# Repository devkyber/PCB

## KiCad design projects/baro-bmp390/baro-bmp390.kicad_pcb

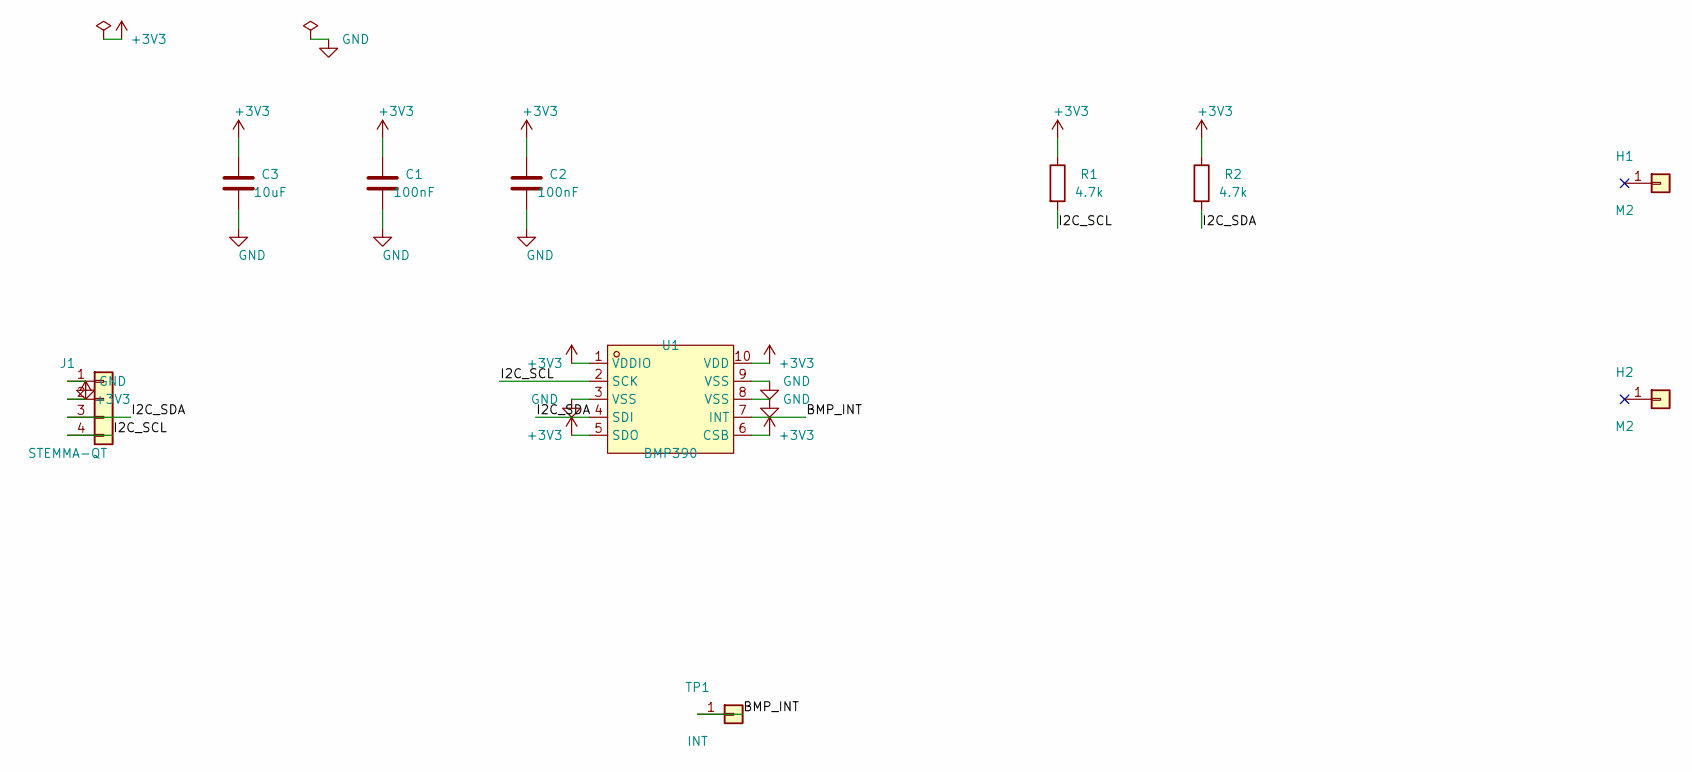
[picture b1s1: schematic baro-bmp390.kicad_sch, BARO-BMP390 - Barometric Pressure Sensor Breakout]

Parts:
C1, C2: 100nF; C_0402_1005Metric
C3: 10uF; C_0603_1608Metric
H1, H2: M2; MountingHole_2.2mm_M2_Pad
J1: STEMMA-QT; JST_SH_SM04B-SRSS-TB_1x04-1MP_P1.00mm_Horizontal
R1, R2: 4.7k; R_0402_1005Metric
TP1: INT; TestPoint_Pad_1.0x1.0mm
U1: BMP390; LGA-10_L2.0-W2.0-P0.50-BL

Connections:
+3V3: C1.1, C2.1, C3.1, J1.2, R1.1, R2.1, U1.1 (VDDIO), U1.5 (SDO), U1.6 (CSB), U1.10 (VDD)
BMP_INT: TP1.1, U1.7 (INT)
GND: C1.2, C2.2, C3.2, J1.1, U1.3 (VSS), U1.8 (VSS), U1.9 (VSS)
I2C_SCL: J1.4, R1.2, U1.2 (SCK)
I2C_SDA: J1.3, R2.2, U1.4 (SDI)

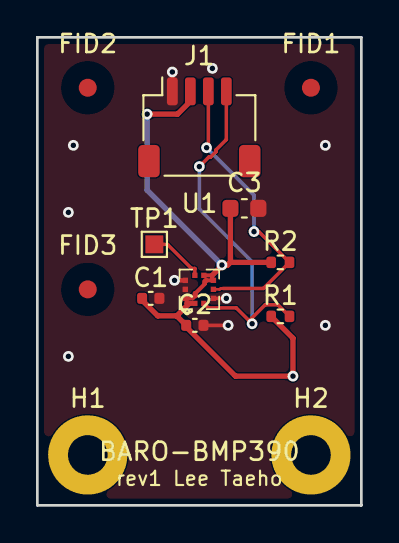
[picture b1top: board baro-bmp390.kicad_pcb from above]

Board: 2 copper layers, 18.0 x 26.0 mm, 13 parts (0 on the bottom side), 5 nets.

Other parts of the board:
FID1, FID2, FID3: FIDUCIAL; Fiducial_1mm_Mask3mm

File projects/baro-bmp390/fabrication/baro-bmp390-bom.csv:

Comment,Designator,Footprint,LCSC Part #
100nF,"C1,C2",C_0402_1005Metric,C307331
10uF,C3,C_0603_1608Metric,C96446
4.7k,"R1,R2",R_0402_1005Metric,C25900
BMP390,U1,LGA-10_L2.0-W2.0-P0.50-BL,C5124834
STEMMA-QT,J1,JST_SH_SM04B-SRSS-TB_1x04-1MP_P1.00mm_Horizontal,C160404

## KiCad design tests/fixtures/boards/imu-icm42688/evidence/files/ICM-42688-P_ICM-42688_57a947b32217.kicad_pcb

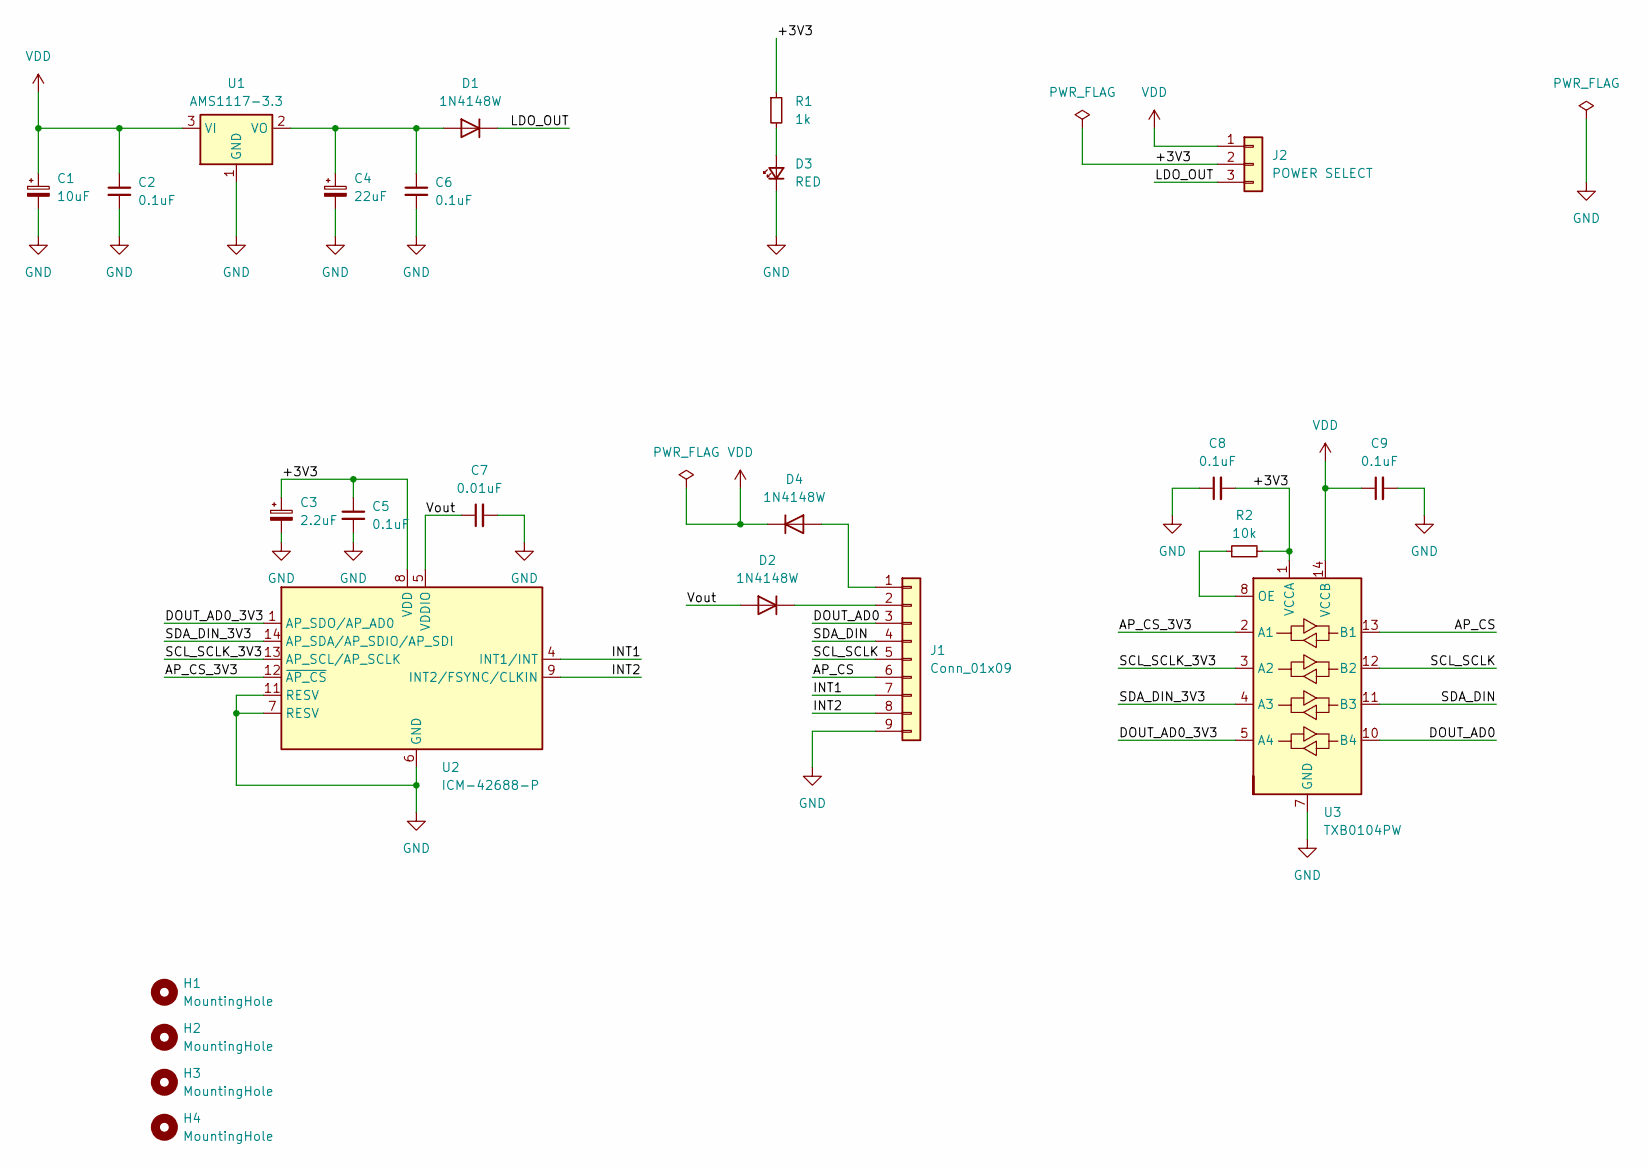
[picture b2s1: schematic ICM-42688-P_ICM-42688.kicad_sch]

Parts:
C1: 10uF; CP_EIA-3528-12_Kemet-T
C2, C5, C6, C8, C9: 0.1uF; C_0603_1608Metric
C3: 2.2uF; CP_EIA-3528-12_Kemet-T
C4: 22uF; CP_EIA-3528-12_Kemet-T
C7: 0.01uF; C_0603_1608Metric
D1, D2, D4: 1N4148W; D_SOD-123
D3: RED; LED_0603_1608Metric
H1, H2, H3, H4: MountingHole; MountingHole_2mm
J1: Conn_01x09; PinHeader_1x09_P2.54mm_Vertical
J2: POWER SELECT; PinHeader_1x03_P2.54mm_Vertical
R1: 1k; R_0603_1608Metric
R2: 10k; R_0603_1608Metric
U1: AMS1117-3.3; SOT-223-3_TabPin2
U2: ICM-42688-P; LGA-14_3x2.5mm_P0.5mm_LayoutBorder3x4y
U3: TXB0104PW; TSSOP-14_4.4x5mm_P0.65mm

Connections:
/+3V3: C3.1, C5.1, C8.2, J2.2, R1.1, R2.2, U2.8 (VDD), U3.1 (VCCA)
/AP_CS: J1.6, U3.13 (B1)
/AP_CS_3V3: U2.12 (~AP_CS), U3.2 (A1)
/DOUT_AD0: J1.3, U3.10 (B4)
/DOUT_AD0_3V3: U2.1 (AP_SDO/AP_AD0), U3.5 (A4)
/INT1: J1.7, U2.4 (INT1/INT)
/INT2: J1.8, U2.9 (INT2/FSYNC/CLKIN)
/LDO_OUT: D1.1 (K), J2.3
/SCL_SCLK: J1.5, U3.12 (B2)
/SCL_SCLK_3V3: U2.13 (AP_SCL/AP_SCLK), U3.3 (A2)
/SDA_DIN: J1.4, U3.11 (B3)
/SDA_DIN_3V3: U2.14 (AP_SDA/AP_SDIO/AP_SDI), U3.4 (A3)
/Vout: C7.1, D2.2 (A), U2.5 (VDDIO)
GND: C1.2, C2.2, C3.2, C4.2, C5.2, C6.2, C7.2, C8.1, C9.2, D3.1 (K), J1.9, U1.1 (GND), U2.6 (GND), U2.7 (RESV), U2.11 (RESV), U3.7 (GND)
unnamed: C4.1, C6.1, D1.2 (A), U1.2 (VO)
unnamed: D2.1 (K), J1.2
unnamed: D3.2 (A), R1.2
unnamed: D4.2 (A), J1.1
unnamed: R2.1, U3.8 (OE)
VDD: C1.1, C2.1, C9.1, D4.1 (K), J2.1, U1.3 (VI), U3.14 (VCCB)

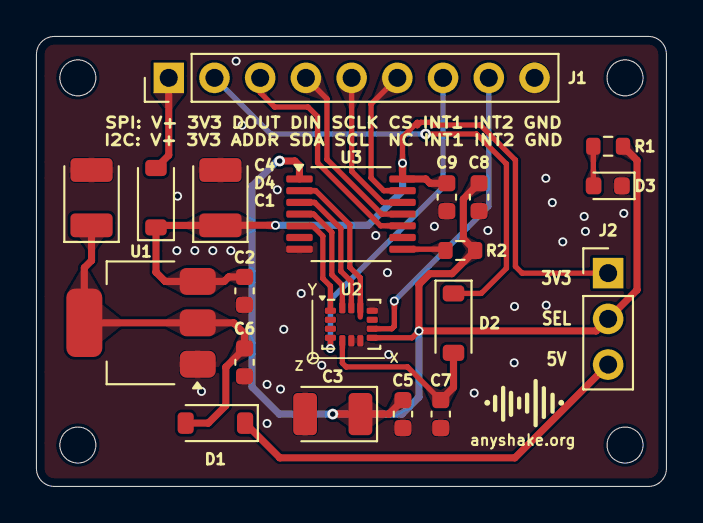
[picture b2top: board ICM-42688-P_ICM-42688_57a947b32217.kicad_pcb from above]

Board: 2 copper layers, 35.0 x 25.0 mm, 24 parts (0 on the bottom side), 20 nets.

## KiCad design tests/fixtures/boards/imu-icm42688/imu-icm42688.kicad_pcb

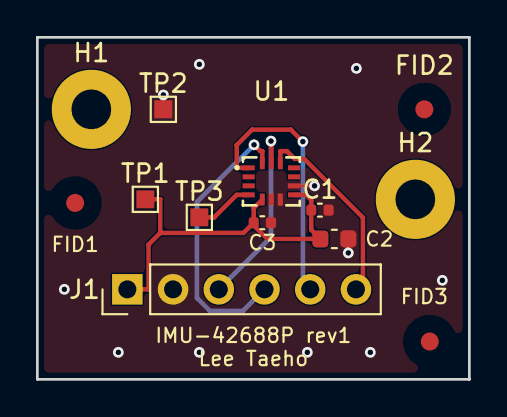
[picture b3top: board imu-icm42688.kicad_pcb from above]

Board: 2 copper layers, 24.0 x 19.0 mm, 13 parts (0 on the bottom side), 7 nets.

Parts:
C1: 100nF; C_0402_1005Metric
C2: 2.2uF; C_0603_1608Metric
C3: 10nF; C_0402_1005Metric
FID1, FID2, FID3: FIDUCIAL; Fiducial_1mm_Mask3mm
H1, H2: M2; MountingHole_2.2mm_M2_Pad
J1: SPI-HDR; PinHeader_1x06_P2.54mm_Vertical
TP1: +3V3; TestPoint_Pad_1.0x1.0mm
TP2: GND; TestPoint_Pad_1.0x1.0mm
TP3: INT1; TestPoint_Pad_1.0x1.0mm
U1: ICM-42688-P; LGA-14_L3.0-W2.5-P0.50-TL

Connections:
+3V3: C1.1, C2.1, C3.1, J1.1, TP1.1, U1.5, U1.8
GND: C1.2, C2.2, C3.2, J1.2, TP2.1, U1.6, U1.7, U1.9
INT1: TP3.1, U1.4
SPI_CS: J1.6, U1.12
SPI_SCLK: J1.3, U1.13
SPI_SDI: J1.4, U1.14
SPI_SDO: J1.5, U1.1

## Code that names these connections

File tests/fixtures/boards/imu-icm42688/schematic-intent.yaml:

schema_version: 1
title: ICM-42688-P SPI breakout
revision: working-1
sheets:
  - id: main
    title: Host interface, inertial sensor and mounting
    page: A4
blocks:
  - id: host
    title: Host SPI and supplied rails
    sheet: main
    flow_order: 1
    placement_hint: left
  - id: sensor
    title: ICM-42688-P and decoupling
    sheet: main
    flow_order: 2
    placement_hint: center
  - id: mechanical
    title: Mounting - owner orientation pending
    sheet: main
    flow_order: 3
    placement_hint: right
components:
  - ref: J1
    value: SPI-HDR
    symbol: Connector_Generic:Conn_01x06
    footprint: Connector_PinHeader_2.54mm:PinHeader_1x06_P2.54mm_Vertical
    block: host
    evidence_part_number: GENERIC-SPI-HEADER-1X06
    pin_map_evidence_id: null
    pin_map_review_note: Preserved accepted Conn_01x06 symbol and netmap; vendor connector numbering and mating orientation remain unverified.
    pins:
      '1': {net: '+3V3', style: power}
      '2': {net: GND, style: power}
      '3': {net: SPI_SCLK, style: label}
      '4': {net: SPI_SDI, style: label}
      '5': {net: SPI_SDO, style: label}
      '6': {net: SPI_CS, style: label}
    pin_inventory: ['1', '2', '3', '4', '5', '6']
  - ref: TP1
    value: '+3V3'
    symbol: Connector_Generic:Conn_01x01
    footprint: TestPoint:TestPoint_Pad_1.0x1.0mm
    block: host
    evidence_part_number: GENERIC-TEST-PAD-1MM
    pin_map_evidence_id: null
    pin_map_review_note: Preserved accepted Conn_01x01 symbol and single-pad footprint; no matching vendor drawing is archived, physical verification remains pending.
    pins:
      '1': {net: '+3V3', style: power}
    pin_inventory: ['1']
  - ref: TP2
    value: GND
    symbol: Connector_Generic:Conn_01x01
    footprint: TestPoint:TestPoint_Pad_1.0x1.0mm
    block: host
    evidence_part_number: GENERIC-TEST-PAD-1MM
    pin_map_evidence_id: null
    pin_map_review_note: Preserved accepted Conn_01x01 symbol and single-pad footprint; no matching vendor drawing is archived, physical verification remains pending.
    pins:
      '1': {net: GND, style: power}
    pin_inventory: ['1']
  - ref: '#FLG01'
    value: PWR_FLAG
    symbol: power:PWR_FLAG
    footprint: '~'
    block: host
    evidence_part_number: KICAD-PWR-FLAG
    pin_map_evidence_id: null
    pin_map_review_note: Preserved accepted KiCad power flag asserting the host-supplied rail; this is an ERC assertion without a vendor component or physical footprint.
    pins:
      '1': {net: '+3V3', style: power}
    pin_inventory: ['1']
  - ref: '#FLG02'
    value: PWR_FLAG
    symbol: power:PWR_FLAG
    footprint: '~'
    block: host
    evidence_part_number: KICAD-PWR-FLAG
    pin_map_evidence_id: null
    pin_map_review_note: Preserved accepted KiCad power flag asserting the host ground; this is an ERC assertion without a vendor component or physical footprint.
    pins:
      '1': {net: GND, style: power}
    pin_inventory: ['1']
  - ref: U1
    value: ICM-42688-P
    symbol: jlcpcb:ICM-42688-P
    footprint: jlcpcb:LGA-14_L3.0-W2.5-P0.50-TL
    block: sensor
    evidence_part_number: ICM-42688-P
    pin_map_evidence_id: sha256:5710af9388adbb311557e99203e5834e17fb0b6e16baf9c09a8bce18b2ce1b9c
    pins:
      '1': {net: SPI_SDO, style: label}
      '4': {net: INT1, style: wire}
      '5': {net: '+3V3', style: power}
      '6': {net: GND, style: power}
      '7': {net: GND, style: power}
      '8': {net: '+3V3', style: power}
      '9': {net: GND, style: power}
      '12': {net: SPI_CS, style: label}
      '13': {net: SPI_SCLK, style: label}
      '14': {net: SPI_SDI, style: label}
    no_connects:
      - {pin: '2', reason: Accepted schematic NC retained; DS-000347 rev 1.6 Table 10 page 20 permits NC or GND for this reserved pin.}
      - {pin: '3', reason: Accepted schematic NC retained; DS-000347 rev 1.6 Table 10 page 20 permits NC or GND for this reserved pin.}
      - {pin: '10', reason: Accepted schematic NC retained; DS-000347 rev 1.6 Table 10 page 20 permits NC or GND for this reserved pin.}
      - {pin: '11', reason: Accepted schematic NC retained; DS-000347 rev 1.6 Table 10 page 20 permits NC or GND for this reserved pin.}
    pin_inventory: ['1', '2', '3', '4', '5', '6', '7', '8', '9', '10', '11', '12', '13', '14']
  - ref: TP3
    value: INT1
    symbol: Connector_Generic:Conn_01x01
    footprint: TestPoint:TestPoint_Pad_1.0x1.0mm
    block: sensor
    evidence_part_number: GENERIC-TEST-PAD-1MM
    pin_map_evidence_id: null
    pin_map_review_note: Preserved accepted Conn_01x01 symbol and single-pad footprint; no matching vendor drawing is archived, physical verification remains pending.
    pins:
      '1': {net: INT1, style: wire}
    pin_inventory: ['1']
  - ref: C1
    value: 100nF
    symbol: Device:C
    footprint: Capacitor_SMD:C_0402_1005Metric
    block: sensor
    evidence_part_number: GENERIC-100NF-0402
    pin_map_evidence_id: null
    pin_map_review_note: Preserved accepted Device:C pin numbering and 0402 footprint; sensor datasheet supports circuit value, not a specific purchased capacitor pin map. Vendor package verification remains pending.
    pins:
      '1': {net: '+3V3', style: power}
      '2': {net: GND, style: power}
    pin_inventory: ['1', '2']
  - ref: C2
    value: 2.2uF
    symbol: Device:C
    footprint: Capacitor_SMD:C_0603_1608Metric
    block: sensor
    evidence_part_number: GENERIC-2.2UF-0603
    pin_map_evidence_id: null
    pin_map_review_note: Preserved accepted Device:C pin numbering and 0603 footprint; sensor datasheet supports circuit value, not a specific purchased capacitor pin map. Vendor package verification remains pending.
    pins:
      '1': {net: '+3V3', style: power}
      '2': {net: GND, style: power}
    pin_inventory: ['1', '2']
  - ref: C3
    value: 10nF
    symbol: Device:C
    footprint: Capacitor_SMD:C_0402_1005Metric
    block: sensor
    evidence_part_number: GENERIC-10NF-0402
    pin_map_evidence_id: null
    pin_map_review_note: Preserved accepted Device:C pin numbering and 0402 footprint; sensor datasheet supports circuit value, not a specific purchased capacitor pin map. Vendor package verification remains pending.
    pins:
      '1': {net: '+3V3', style: power}
      '2': {net: GND, style: power}
    pin_inventory: ['1', '2']
  - ref: H1
    value: M2
    symbol: Connector_Generic:Conn_01x01
    footprint: MountingHole:MountingHole_2.2mm_M2_Pad
    block: mechanical
    evidence_part_number: GENERIC-M2-PLATED-MOUNTING-HOLE
    pin_map_evidence_id: null
    pin_map_review_note: Preserved accepted Conn_01x01 symbol and plated M2 hole footprint; mechanical drawing and assembly verification remain pending.
    pins: {}
    no_connects:
      - {pin: '1', reason: Accepted schematic explicitly marks the mounting-hole pad NC; no ground connection is added.}
    pin_inventory: ['1']
  - ref: H2
    value: M2
    symbol: Connector_Generic:Conn_01x01
    footprint: MountingHole:MountingHole_2.2mm_M2_Pad
    block: mechanical
    evidence_part_number: GENERIC-M2-PLATED-MOUNTING-HOLE
    pin_map_evidence_id: null
    pin_map_review_note: Preserved accepted Conn_01x01 symbol and plated M2 hole footprint; mechanical drawing and assembly verification remain pending.
    pins: {}
    no_connects:
      - {pin: '1', reason: Accepted schematic explicitly marks the mounting-hole pad NC; no ground connection is added.}
    pin_inventory: ['1']
boundary_nets: [SPI_SCLK, SPI_SDI, SPI_SDO, SPI_CS]

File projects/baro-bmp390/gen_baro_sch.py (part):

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      desc='STEMMA QT / Qwiic I2C connector, JST SH 4-pin 1mm pitch')
pin_label('J1', '1', 'GND')
pin_label('J1', '2', '+3V3')
pin_label('J1', '3', 'I2C_SDA')
pin_label('J1', '4', 'I2C_SCL')


# PWR_FLAG: host supplies +3V3 via the STEMMA QT connector — ERC can't
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place('Device', 'R', 'R1', '4.7k', 165, 150,
      fp='Resistor_SMD:R_0402_1005Metric',
      desc='I2C SCL pull-up to VDDIO — Bosch datasheet Fig.25 recommended 4.7kOhm')
pin_label('R1', '1', '+3V3'); pin_label('R1', '2', 'I2C_SCL')

place('Device', 'R', 'R2', '4.7k', 185, 150,
      fp='Resistor_SMD:R_0402_1005Metric',
      desc='I2C SDA pull-up to VDDIO — Bosch datasheet Fig.25 recommended 4.7kOhm')
pin_label('R2', '1', '+3V3'); pin_label('R2', '2', 'I2C_SDA')

place('Connector_Generic', 'Conn_01x01', 'TP1', 'INT', 120, 75,
      fp='TestPoint:TestPoint_Pad_1.0x1.0mm',
      desc='BMP390 INT breakout test point (unused in V1, routed per §15.2)')
pin_label('TP1', '1', 'BMP_INT')

# --- Pin-accurate nets on U1 (BMP390), direct to real pin coordinates ---
pin_label('U1', '1', '+3V3')     # VDDIO
pin_label('U1', '2', 'I2C_SCL')  # SCK / SCL
pin_label('U1', '3', 'GND')      # VSS
pin_label('U1', '4', 'I2C_SDA')  # SDI / SDA
pin_label('U1', '5', '+3V3')     # SDO — tied to VDDIO -> I2C address 0x77
pin_label('U1', '6', '+3V3')     # CSB — tied to VDDIO -> selects I2C mode
pin_label('U1', '7', 'BMP_INT')  # INT
pin_label('U1', '8', 'GND')      # VSS
pin_label('U1', '9', 'GND')      # VSS
pin_label('U1', '10', '+3V3')    # VDD
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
